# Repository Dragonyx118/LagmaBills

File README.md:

# L.A.G.M.A. B.I.L.L.S.
**L**and **A**nd **G**round-to-**M**idair **A**gent — **B**uilt for **I**ntelligent **L**inked **L**ocal **S**upport

A Mecanum-wheeled robot for civil protection, powered by a Raspberry Pi orchestrating two custom ESP32 PCBs, sensors, a robotic arm, and a drone companion over MQTT. It navigates autonomously, maps its environment, avoids obstacles, and is controlled via voice AI, a MAUI app, or browser dashboard.

Presentato ad Arduino Day 2025.

## Team
- **Daniele Cerioli (Dragonyx)** — firmware, software, PCB, integrazione di sistema
- **Simone Panelli (Tabella_Brodosa)** — componenti AI
- **Andrei Corduneanu** — modellazione 3D, falegnameria

## Repositories

| Repo | Contenuto |
|---|---|
| `lagmabills` (questo) | Firmware ESP32, codice Python Raspberry Pi, PCB (KiCad), modelli 3D |
| [`lagmabills-app`](https://github.com/Dragonyx118/LagmaIpp) | App companion LagmaIpp (.NET MAUI, Windows + Android) |
| [`lagmabills-web`](https://github.com/Dragonyx118/LagmaBills-Web) | Sito web del progetto |

## Struttura del repository

```
lagmabills/
├── firmware/
│   ├── firm_esp32_motori/     # Firmware PCBmotori (PlatformIO)
│   └── firm_esp32_sensori/    # Firmware PCBsensori (PlatformIO)
├── raspberry/
│   ├── odometria.py           # Odometria encoder Mecanum
│   ├── occupancyGrid.py       # Mappatura locale log-odds
│   ├── navigator.py           # Navigazione autonoma Potential Field
│   ├── GPS.py                 # Lettura NEO-6M → MQTT
│   ├── myViewerServer.py      # Dashboard web (HTTP + WebSocket + Leaflet)
│   ├── rasp_cam/              # Streaming camera OV5647
│   ├── odo_module/            # Moduli navigazione/mappatura aggiuntivi
│   └── Bamberg/
│       ├── ESP-IDF/           # Firmware ESP-Drone (ESP-IDF)
│       └── firm_drone/        # Bridge MQTT ↔ CRTP/UDP drone + test
├── AI_Bepo/                   # Server AI vocale (wakeword, STT, LLM, TTS)
├── AmazingArm/                # Modelli e risorse braccio robotico
├── PCB/
│   ├── PCBmotori/             # KiCad — ESP32 motori (4-layer)
│   ├── PCBsensori/            # KiCad — ESP32 sensori
│   └── PCBalim/               # KiCad — distribuzione alimentazione
├── Hardware/                  # Datasheet, pinout, power budget, BOM
├── models_3d/                 # Modelli 3D stampabili
└── docs/
    ├── img/                   # Foto e video dimostrativi
    └── LAGMABILLS.pptx        # Presentazione progetto
```

## Hardware

| Componente | Descrizione |
|---|---|
| Raspberry Pi 4B (4GB) | Cervello centrale, broker MQTT, Tailscale VPN |
| PCBmotori (ESP32, 4-layer) | 4× JGA25-370 Mecanum + encoder, 2× TB6612FNG, I2C slave 0x08 |
| PCBsensori (ESP32) | 6× HC-SR04, MPU-6050, 3× TCRT5000, PCA9685 → braccio 6DOF, I2C slave 0x09 |
| PCBalim | Distribuzione alimentazione custom, 2× LiPo 3S 5500mAh |
| ESP-Drone (ESP32-S2) | Ricognizione aerea, CRTP/UDP |
| OV5647 CSI | Camera RPi, stream MJPEG |
| ReSpeaker 2-Mic HAT | WM8960, wakeword ONNX, DOA GCC-PHAT |
| NEO-6M GPS | Tracciamento posizione world frame |
| Display 7" HDMI | Faccia animata responsiva (RPi) |
| Speaker Bluetooth | Audio stereo, musica / sirene / TTS |

Dettagli completi in [`Hardware/BOM.xlsx`](Hardware/BOM.xlsx) e [`Hardware/pinoutEsp32.xlsx`](Hardware/pinoutEsp32.xlsx).

## Architettura software

Tutto comunica via MQTT (Mosquitto su RPi, `localhost:1883`, accessibile anche via Tailscale).

```
              ┌─────────────────────────┐
              │  Mosquitto Broker (RPi) │
              └────────────┬────────────┘
     ┌──────────┬──────────┼──────────┬──────────┐
     │          │          │          │          │
odometria   occupancy   navigator  drone_bridge  GPS
     │        grid.py      .py        .py       .py
     │          │
  robot/     robot/
 motori/     mappa/
 stato       grid
```

| Topic | Direzione | Descrizione |
|---|---|---|
| `robot/motori/cmd` | Pi → ESP32 | Comandi movimento |
| `robot/motori/stato` | ESP32 → Pi | Encoder + PWM |
| `robot/sensori/distanze` | ESP32 → Pi | Distanze HC-SR04 (cm) |
| `robot/sensori/imu` | ESP32 → Pi | Accelerometro + giroscopio |
| `robot/odometria` | Pi → tutti | Posa X, Y, θ |
| `robot/mappa/grid` | Pi → viewer | Occupancy grid JSON |
| `robot/cliff/stato` | Pi → tutti | Stato sensori cliff |
| `robot/nav/cmd` | app → Pi | start / stop / reset_goal |
| `robot/nav/goal` | app → Pi | Goal `{x, y}` in world frame |
| `drone/cmd/rpyt` | app → Pi | Roll, pitch, yaw, thrust |

## Installazione (Raspberry Pi)

```bash
# Dipendenze Python
pip install paho-mqtt numpy sounddevice onnxruntime websockets \
            flask flask-socketio pyserial pynmea2 faster-whisper psutil

# Mosquitto broker
sudo apt install mosquitto mosquitto-clients
sudo systemctl enable mosquitto

# Driver ReSpeaker 2-Mic HAT
# Seguire istruzioni in Hardware/ o repo seeed-voicecard

# Avviare i moduli (esempio)
python3 raspberry/odometria.py &
python3 raspberry/occupancyGrid.py &
python3 raspberry/navigator.py &
python3 raspberry/GPS.py &
python3 raspberry/myViewerServer.py &
```

Dashboard web: `http://<ip-pi>:8080`

## Firmware ESP32 (PlatformIO)

Le cartelle in `firmware/` sono progetti PlatformIO completi e pronti da compilare (`pio run`).

Librerie richieste (`platformio.ini`):
- PubSubClient
- ArduinoJson
- MPU6050_light
- Adafruit PWM Servo Driver
- Preferences

Le credenziali WiFi e broker MQTT vengono salvate in NVS e possono essere aggiornate via I2C dal Pi senza reflashare.

📦 **Non vuoi compilare tu stesso?** Scarica le cartelle sorgente aggiornate automaticamente ad ogni modifica dalla sezione [Releases](../../releases).

## Pipeline AI vocale

```
ReSpeaker mic → wakeword ("hey nova") → DOA GCC-PHAT (stima direzione)
    → WebSocket stream PCM16 raw
    → Whisper STT → LLM (Ollama) → Piper TTS (voce "Miro" italiano)
    → audio risposta → Speaker Bluetooth
```

## Demo

**Primi test di movimento**

https://github.com/Dragonyx118/LagmaBills/raw/main/docs/img/first_test_move.mp4

**Prototipo in movimento**

https://github.com/Dragonyx118/LagmaBills/raw/main/docs/img/proto_move.mp4

**Test braccio robotico**

https://github.com/Dragonyx118/LagmaBills/raw/main/docs/img/test_arm.mp4

**Struttura in legno**

https://github.com/Dragonyx118/LagmaBills/raw/main/docs/img/wood_body.mp4

> GitHub riproduce automaticamente i link diretti `.mp4` di un repository quando incollati su una riga propria nel README, mostrando un player inline.

## Licenza

[Hippocratic License 3.0](LICENSE) (HL3-CL-ECO-LAW-MIL-SV) — © 2025 Dragonyx

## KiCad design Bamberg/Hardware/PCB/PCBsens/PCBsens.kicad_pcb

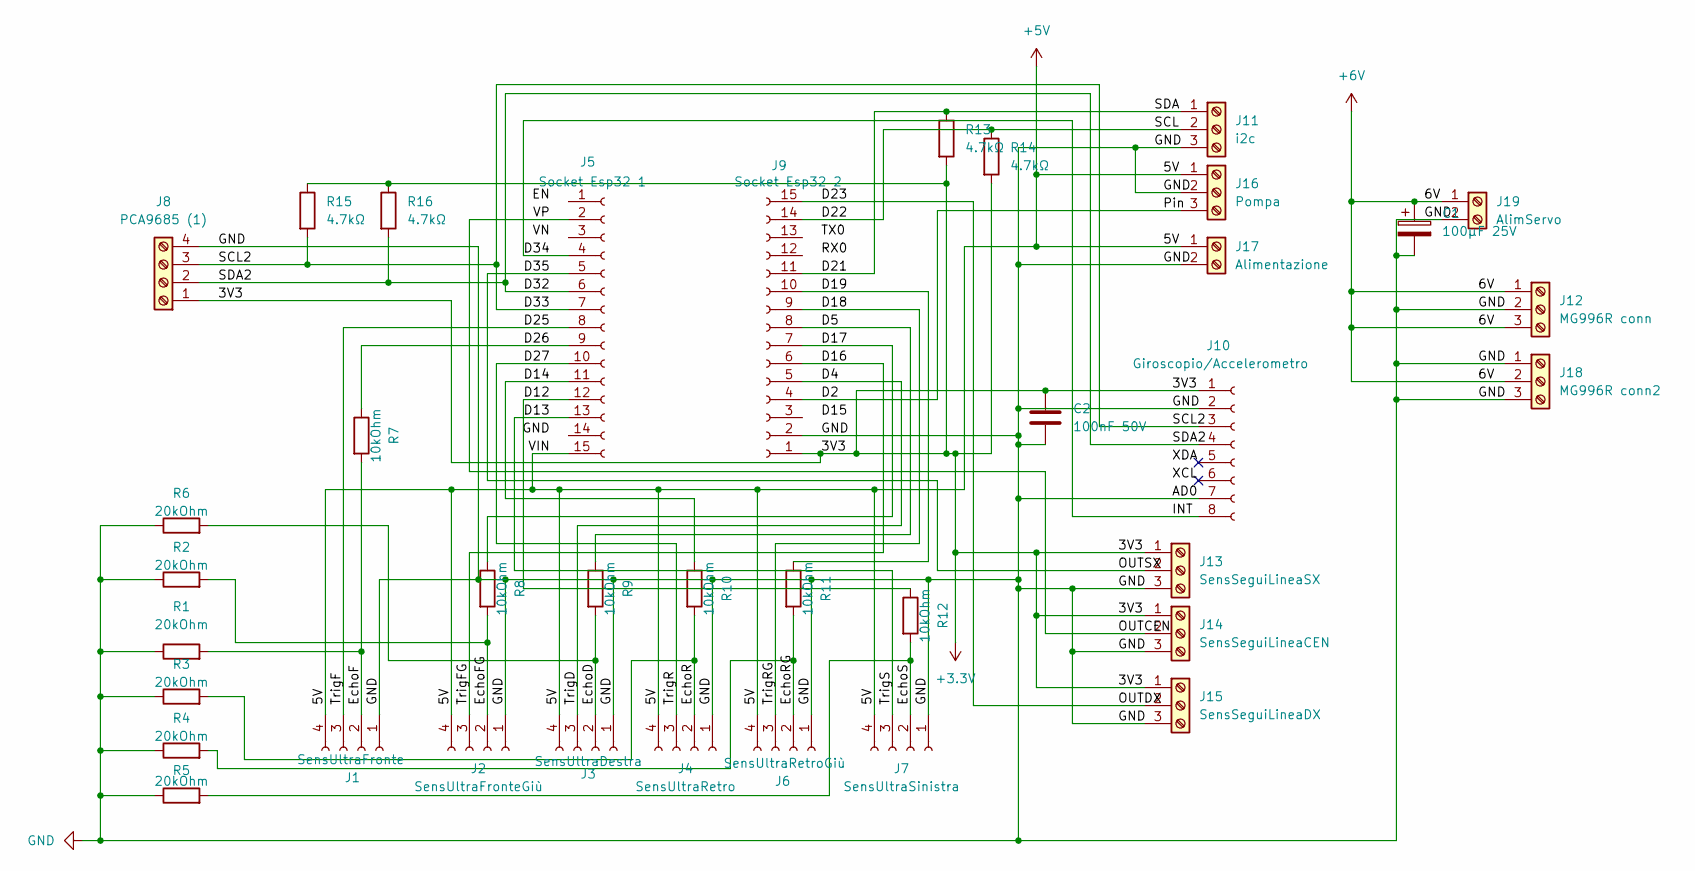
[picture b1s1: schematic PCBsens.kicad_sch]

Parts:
C1: 100µF 25V; CP_Radial_D8.0mm_P3.50mm
C2: 100nF 50V; C_Disc_D5.0mm_W2.5mm_P5.00mm
J1: SensUltraFronte; PinSocket_1x04_P2.54mm_Vertical
J2: SensUltraFronteGiù; PinSocket_1x04_P2.54mm_Vertical
J3: SensUltraDestra; PinSocket_1x04_P2.54mm_Vertical
J4: SensUltraRetro; PinSocket_1x04_P2.54mm_Vertical
J5: Socket Esp32 1; PinSocket_1x15_P2.54mm_Vertical
J6: SensUltraRetroGiù; PinSocket_1x04_P2.54mm_Vertical
J7: SensUltraSinistra; PinSocket_1x04_P2.54mm_Vertical
J8: PCA9685 (1); TerminalBlock_Phoenix_MKDS-1,5-4_1x04_P5.00mm_Horizontal
J9: Socket Esp32 2; PinSocket_1x15_P2.54mm_Vertical
J10: Giroscopio/Accelerometro; PinSocket_1x08_P2.54mm_Vertical
J11: i2c; TerminalBlock_Phoenix_MKDS-1,5-3_1x03_P5.00mm_Horizontal
J12: MG996R conn; TerminalBlock_Phoenix_MKDS-1,5-3_1x03_P5.00mm_Horizontal
J13: SensSeguiLineaSX; PinSocket_1x03_P2.54mm_Vertical
J14: SensSeguiLineaCEN; PinSocket_1x03_P2.54mm_Vertical
J15: SensSeguiLineaDX; PinSocket_1x03_P2.54mm_Vertical
J16: Pompa; TerminalBlock_Phoenix_MKDS-1,5-3_1x03_P5.00mm_Horizontal
J17: Alimentazione; TerminalBlock_Phoenix_MKDS-1,5-2_1x02_P5.00mm_Horizontal
J18: MG996R conn2; TerminalBlock_Phoenix_MKDS-1,5-3_1x03_P5.00mm_Horizontal
J19: AlimServo; TerminalBlock_Phoenix_MKDS-1,5-2_1x02_P5.00mm_Horizontal
R1, R2, R3, R4, R5, R6: 20kOhm; R_Axial_DIN0207_L6.3mm_D2.5mm_P7.62mm_Horizontal
R7, R8, R9, R10, R11, R12: 10kOhm; R_Axial_DIN0207_L6.3mm_D2.5mm_P7.62mm_Horizontal
R13, R14, R15, R16: 4.7kΩ; R_Axial_DIN0207_L6.3mm_D2.5mm_P7.62mm_Horizontal

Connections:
+3.3V: C2.1, J8.1, J9.1, J10.1, J13.1, J14.1, J15.1, R13.2, R14.2, R15.1, R16.1
+5V: J1.4, J2.4, J3.4, J4.4, J5.15, J6.4, J7.4, J16.1, J17.1
+6V: C1.1, J12.1, J12.3, J18.2, J19.1
/D2: J9.4, J16.3
/D4: J3.3, J9.5
/D5: J9.8, R9.1
/D12: J5.12, R12.1
/D13: J5.13, J7.3
/D14: J5.11, R10.1
/D16: J2.3, J9.6
/D17: J9.7, R8.1
/D18: J6.3, J9.9
/D19: J9.10, R11.1
/D21: J9.11, J11.1, R13.1
/D22: J9.14, J11.2, R14.1
/D23: J9.15, J15.2
/D25: J1.3, J5.8
/D26: J5.9, R7.1
/D27: J4.3, J5.10
/D32: J5.6, J8.2, J10.4, R16.2
/D33: J5.7, J8.3, J10.3, R15.2
/D34: J5.4, J10.8
/D35: J5.5, J13.2
/EchoD: J3.2, R6.2, R9.2
/EchoF: J1.2, R1.2, R7.2
/EchoFG: J2.2, R2.2, R8.2
/EchoR: J4.2, R3.2, R10.2
/EchoRG: J6.2, R4.2, R11.2
/EchoS: J7.2, R5.2, R12.2
/OUTCEN: J5.2, J14.2
GND: C1.2, C2.2, J1.1, J2.1, J3.1, J4.1, J6.1, J7.1, J8.4, J9.2, J10.2, J10.7, J11.3, J12.2, J13.3, J14.3, J15.3, J16.2, J17.2, J18.1, J18.3, J19.2, R1.1, R2.1, R3.1, R4.1, R5.1, R6.1

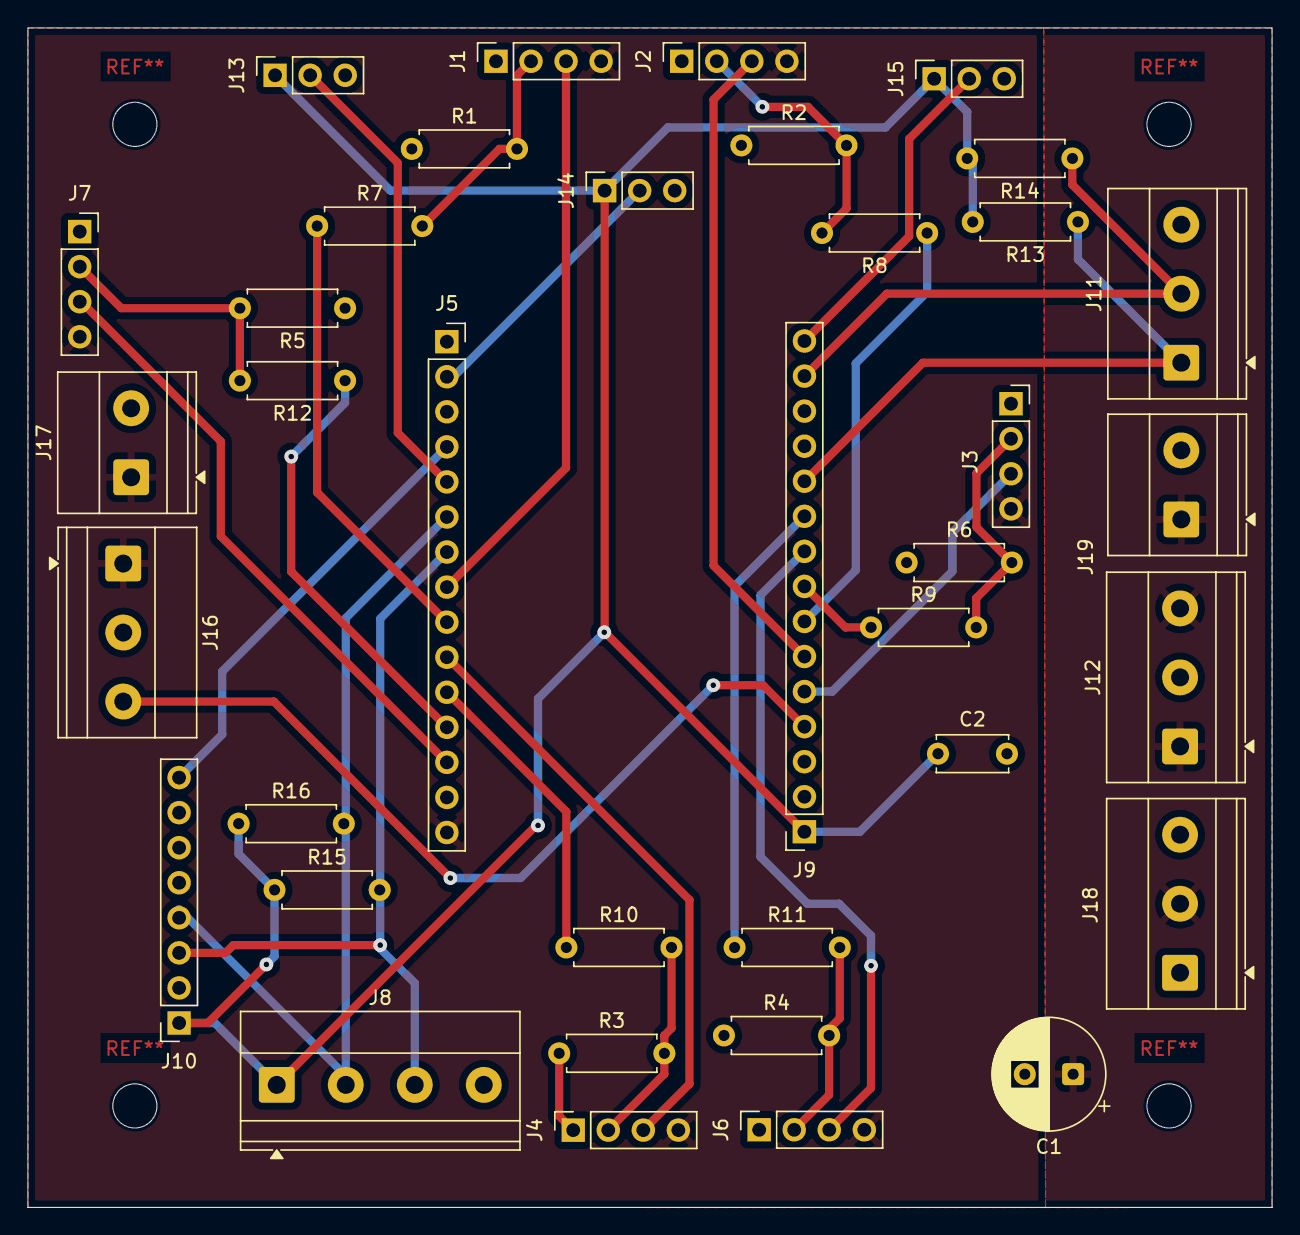
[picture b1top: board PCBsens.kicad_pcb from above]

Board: 2 copper layers, 90.1 x 85.5 mm, 37 parts (0 on the bottom side), 31 nets.

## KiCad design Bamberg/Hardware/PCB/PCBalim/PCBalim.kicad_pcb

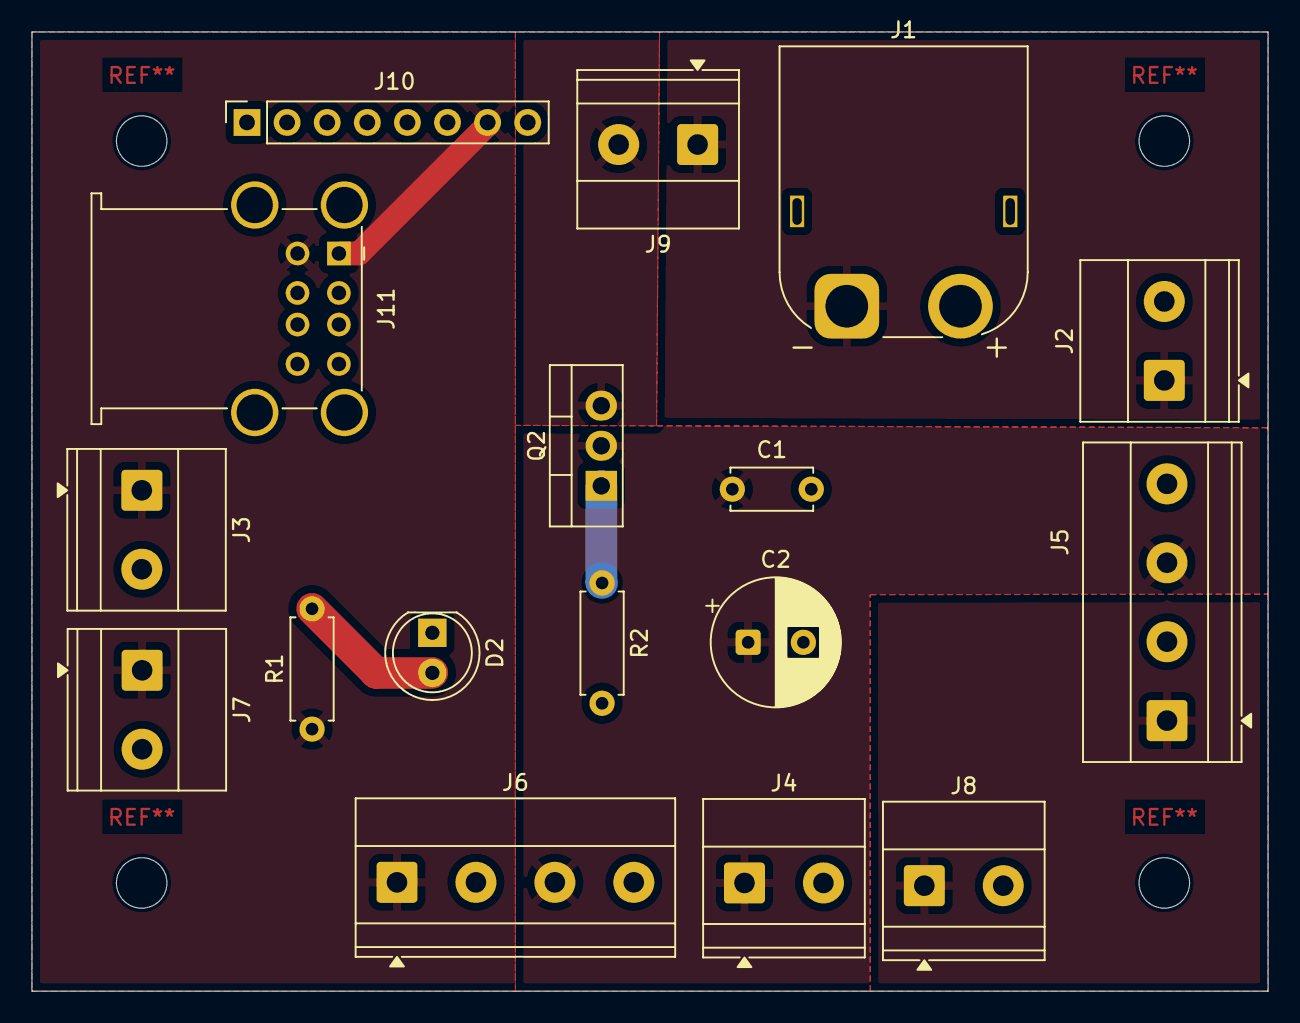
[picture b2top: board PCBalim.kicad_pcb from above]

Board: 2 copper layers, 78.3 x 60.8 mm, 17 parts (0 on the bottom side), 8 nets.

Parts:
C1: Ceramico 100nF (50V); C_Disc_D5.0mm_W2.5mm_P5.00mm
C2: Elettronico 100µF (35V); CP_Radial_D8.0mm_P3.50mm
D2: LED; LED_D5.0mm
J1: XT60PW-M; AMASS_XT60PW-M_1x02_P7.20mm_Horizontal
J2: AlimTest; TerminalBlock_Phoenix_MKDS-1,5-2_1x02_P5.00mm_Horizontal
J3: 5V (OFE); TerminalBlock_Phoenix_MKDS-1,5-2_1x02_P5.00mm_Horizontal
J4: 12V (OFE); TerminalBlock_Phoenix_MKDS-1,5-2_1x02_P5.00mm_Horizontal
J5: 12Vout(for6V); TerminalBlock_Phoenix_MKDS-1,5-4_1x04_P5.00mm_Horizontal
J6: 12Vout(5Vin); TerminalBlock_Phoenix_MKDS-1,5-4_1x04_P5.00mm_Horizontal
J7: 5V (OFE)2; TerminalBlock_Phoenix_MKDS-1,5-2_1x02_P5.00mm_Horizontal
J8: 6V (OFE)2; TerminalBlock_Phoenix_MKDS-1,5-2_1x02_P5.00mm_Horizontal
J9: FUSE HOLDER (IN-OUT); TerminalBlock_Phoenix_MKDS-1,5-2_1x02_P5.00mm_Horizontal
J10: ConnBreakOutUSBC; PinSocket_1x08_P2.54mm_Vertical
J11: USB_A (ToESPDRONE/DISPLAY); USB_A_Wuerth_61400826021_Horizontal_Stacked
Q2: IRF4905; TO-220-3_Vertical
R1: 560 Ohm; R_Axial_DIN0207_L6.3mm_D2.5mm_P7.62mm_Horizontal
R2: 10k Ohm; R_Axial_DIN0207_L6.3mm_D2.5mm_P7.62mm_Horizontal

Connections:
+5V: J3.1, J6.1, J7.1, J10.7, J11.1 (VBUS1), J11.5 (VBUS2), R1.1
+6V: J5.1, J8.1
+12V: C1.1, C2.1, J4.1, J5.3, J6.3, Q2.2 (D)
/12Out: J1.1, J2.1, J9.1
/12Vin: J9.2, Q2.3 (S)
GND: C1.2, C2.2, D2.1 (K), J1.2, J2.2, J3.2, J4.2, J5.2, J5.4, J6.2, J6.4, J7.2, J8.2, J10.8, J11.4 (GND1), J11.8 (GND2), J11.9 (Shield), R2.2
unnamed: D2.2 (A), R1.2
unnamed: Q2.1 (G), R2.1

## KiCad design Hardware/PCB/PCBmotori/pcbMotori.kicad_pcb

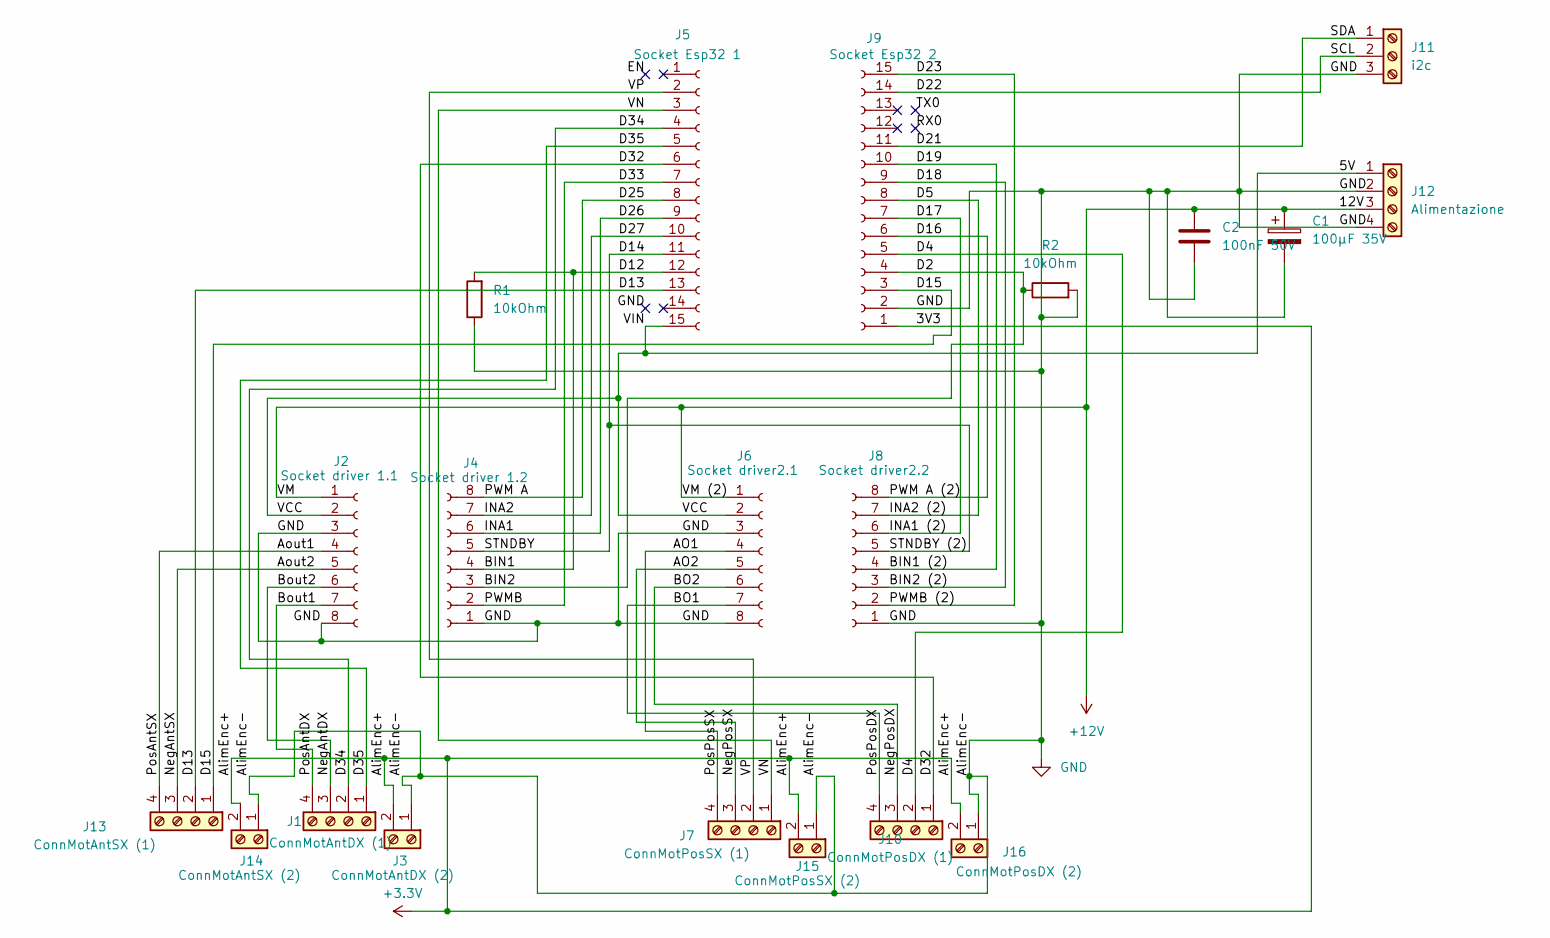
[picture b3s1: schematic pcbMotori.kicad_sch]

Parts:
C1: 100µF 35V; CP_Radial_D8.0mm_P3.50mm
C2: 100nF 50V; C_Disc_D5.0mm_W2.5mm_P5.00mm
J1: ConnMotAntDX (1); TerminalBlock_Phoenix_MKDS-1,5-4_1x04_P5.00mm_Horizontal
J2: Socket driver 1.1; PinSocket_1x08_P2.54mm_Vertical
J3: ConnMotAntDX (2); TerminalBlock_Phoenix_MKDS-1,5-2_1x02_P5.00mm_Horizontal
J4: Socket driver 1.2; PinSocket_1x08_P2.54mm_Vertical
J5: Socket Esp32 1; PinSocket_1x15_P2.54mm_Vertical
J6: Socket driver2.1; PinSocket_1x08_P2.54mm_Vertical
J7: ConnMotPosSX (1); TerminalBlock_Phoenix_MKDS-1,5-4_1x04_P5.00mm_Horizontal
J8: Socket driver2.2; PinSocket_1x08_P2.54mm_Vertical
J9: Socket Esp32 2; PinSocket_1x15_P2.54mm_Vertical
J10: ConnMotPosDX (1); TerminalBlock_Phoenix_MKDS-1,5-4_1x04_P5.00mm_Horizontal
J11: i2c; PinSocket_1x03_P2.54mm_Vertical
J12: Alimentazione; TerminalBlock_Phoenix_MKDS-1,5-4_1x04_P5.00mm_Horizontal
J13: ConnMotAntSX (1); TerminalBlock_Phoenix_MKDS-1,5-4_1x04_P5.00mm_Horizontal
J14: ConnMotAntSX (2); TerminalBlock_Phoenix_MKDS-1,5-2_1x02_P5.00mm_Horizontal
J15: ConnMotPosSX (2); TerminalBlock_Phoenix_MKDS-1,5-2_1x02_P5.00mm_Horizontal
J16: ConnMotPosDX (2); TerminalBlock_Phoenix_MKDS-1,5-2_1x02_P5.00mm_Horizontal
R1, R2: 10kOhm; R_Axial_DIN0207_L6.3mm_D2.5mm_P7.62mm_Horizontal

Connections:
+3.3V: J3.2, J9.1, J14.2, J15.2, J16.2
+12V: C1.1, C2.1, J2.1, J6.1, J12.3
/5V: J2.2, J5.15, J6.2, J12.1
/AO1: J6.4, J7.4
/AO2: J6.5, J7.3
/Aout1: J2.4, J13.4
/Aout2: J2.5, J13.3
/BIN1: J4.4, J5.12, R1.2
/BIN1 (2): J8.4, J9.10
/BIN2: J4.3, J9.4, R2.1
/BIN2 (2): J8.3, J9.9
/BO1: J6.7, J10.4
/BO2: J6.6, J10.3
/Bout1: J1.4, J2.7
/Bout2: J1.3, J2.6
/D4: J9.5, J10.2
/D5: J8.7, J9.8
/D13: J5.13, J13.2
/D14: J4.5, J5.11, J8.5
/D15: J9.3, J13.1
/D16: J8.8, J9.6
/D17: J8.6, J9.7
/D21: J9.11, J11.1
/D22: J9.14, J11.2
/D23: J8.2, J9.15
/D25: J4.8, J5.8
/D26: J4.6, J5.9
/D27: J4.7, J5.10
/D32: J5.6, J10.1
/D33: J4.2, J5.7
/D34: J1.2, J5.4
/D35: J1.1, J5.5
/VN: J5.3, J7.1
/VP: J5.2, J7.2
GND: C1.2, C2.2, J2.3, J2.8, J3.1, J4.1, J6.3, J6.8, J8.1, J9.2, J11.3, J12.2, J12.4, J14.1, J15.1, J16.1, R1.1, R2.2

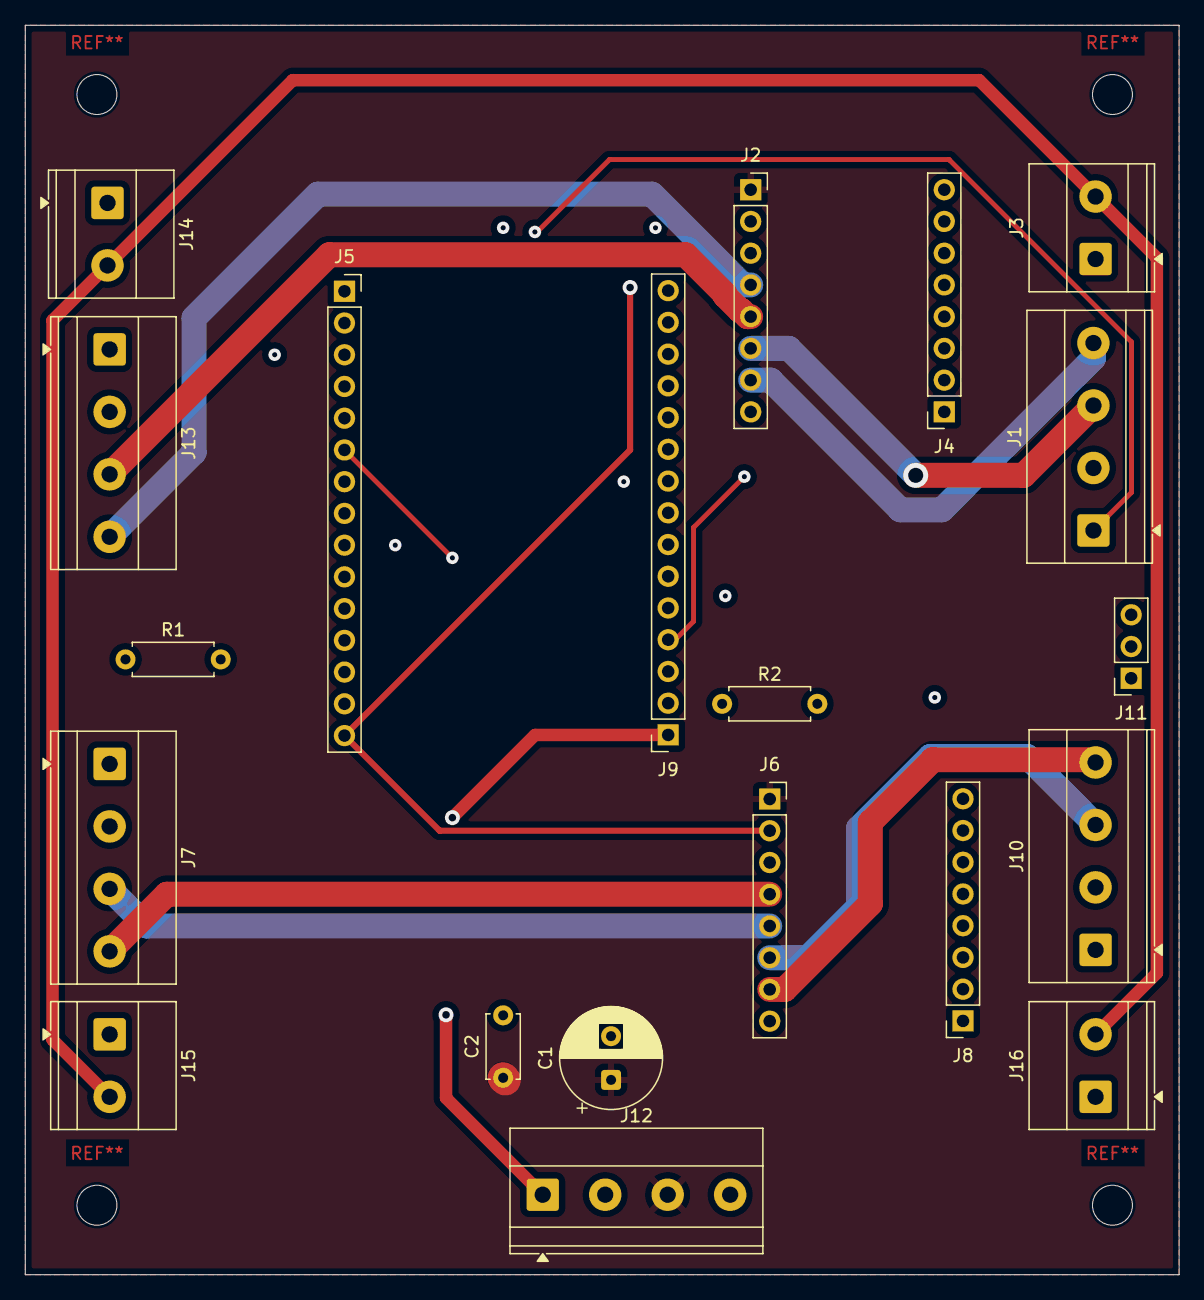
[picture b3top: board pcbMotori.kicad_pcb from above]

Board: 4 copper layers, 92.3 x 100.0 mm, 20 parts (0 on the bottom side), 35 nets.

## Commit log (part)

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2026-05-29 Add hardware base
2026-05-29 Add PCB motori
2026-05-29 Add PCB alim
2026-06-03 Aggiunta cartella Bamberg completa
2026-06-03 Aggiunta cartella Bamberg
2026-06-03 Aggiunta cartella datasheet
2026-06-03 Rinominata cartella DataShit in Datasheet
2026-06-03 Aggiunta cartella AMAZING BALLS
2026-06-03 Rinominata cartella AMAZING BALLS in AmazingArm
2026-06-03 Aggiunta cartella SogmaLigo
2026-06-03 Aggiunta cartella bepo
2026-06-03 Sigman Fraude
2026-06-05 Upload firmware 04/06/2026
2026-06-05 Upload app graphics
2026-06-05 Upload necessary Doom game
2026-06-10 Update LICENSE
2026-06-29 Updated with 3dModels, RaspCam module, Media module

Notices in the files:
README.md:
License: Hippocratic 3.0
